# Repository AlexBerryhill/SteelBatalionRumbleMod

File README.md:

# SteelBatalionRumbleMod
 A KiCad8 pcb for the steel batalion rumble controller mod for the X-Box
 
Based off of the protoboard built in https://web.archive.org/web/20160402001949/http://www.bigmech.com/sb/sb_controller_mod/disclaimer.html

production folder in RumbleMod Folder holds everything needed to print in JLCPCB.

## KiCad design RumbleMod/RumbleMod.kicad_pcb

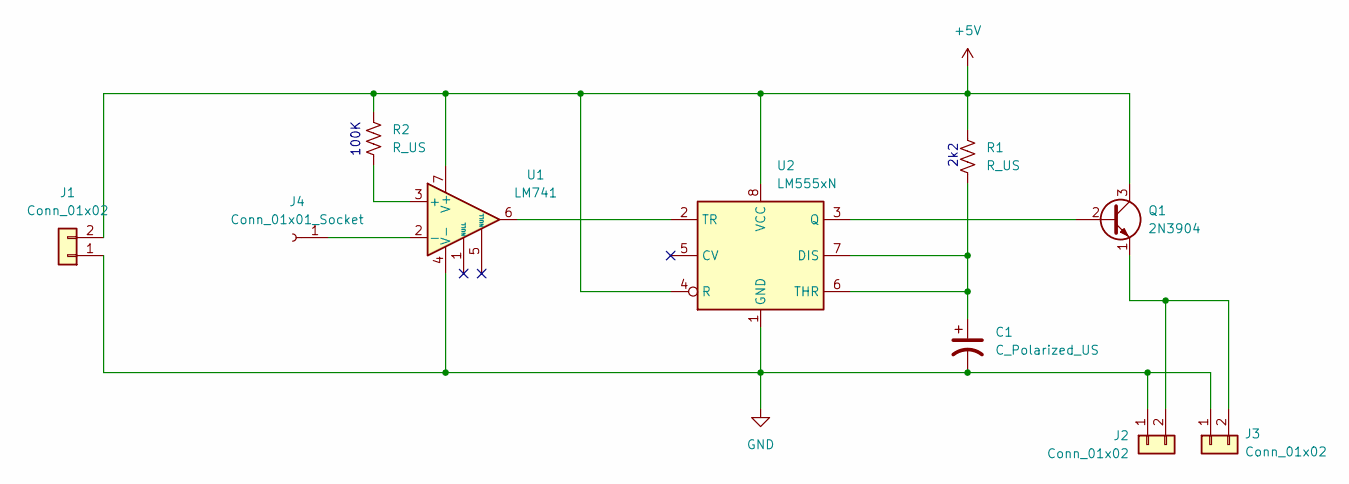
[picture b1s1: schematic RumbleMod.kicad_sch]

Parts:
C1: C_Polarized_US
J1, J2, J3: Conn_01x02; Molex_KK-254_AE-6410-02A_1x02_P2.54mm_Vertical
J4: Conn_01x01_Socket; JST_XH_B1B-XH-AM_1x01_P2.50mm_Vertical
Q1: 2N3904; TO-92_Inline
R1, R2: R_US; R_Axial_DIN0207_L6.3mm_D2.5mm_P10.16mm_Horizontal
U1: LM741; DIP-8_W7.62mm
U2: LM555xN; DIP-8_W7.62mm

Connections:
+5V: J1.2, Q1.3 (C), R1.1, R2.1, U1.7 (V+), U2.4 (R), U2.8 (VCC)
GND: C1.2, J1.1, J2.1, J3.1, U1.4 (V-), U2.1 (GND)
unnamed: J2.2, J3.2, Q1.1 (E)
unnamed: J4.1, U1.2 (-)
unnamed: Q1.2 (B), U2.3 (Q)
unnamed: R2.2, U1.3 (+)
unnamed: C1.1, R1.2, U2.6 (THR), U2.7 (DIS)
unnamed: U1.6, U2.2 (TR)

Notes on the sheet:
2k2
100K

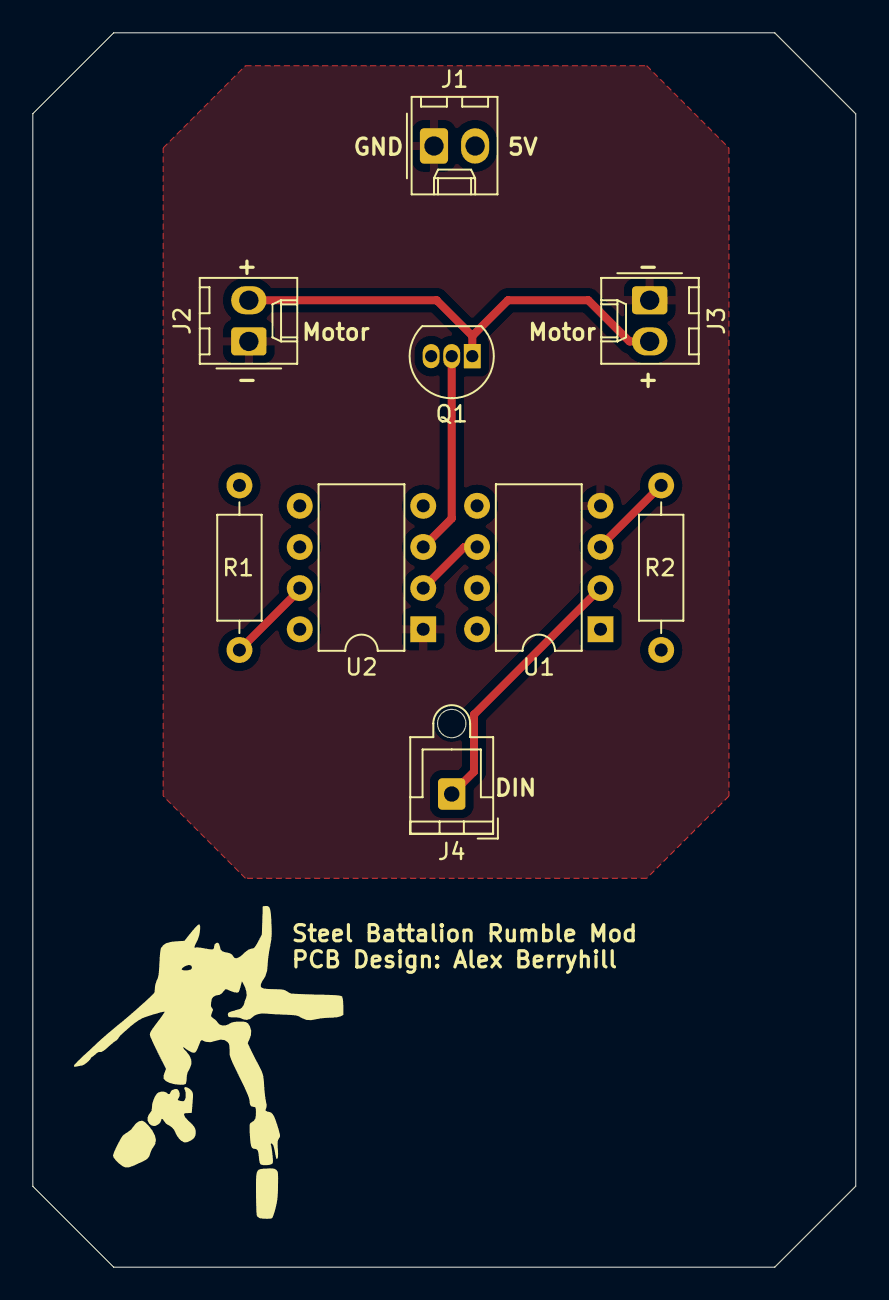
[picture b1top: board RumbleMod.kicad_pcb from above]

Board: 2 copper layers, 50.8 x 76.2 mm, 9 parts (0 on the bottom side), 8 nets.

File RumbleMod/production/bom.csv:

Designator,Footprint,Quantity,Value,LCSC Part #
"J1, J2, J3",Molex_KK-254_AE-6410-02A_1x02_P2.54mm_Vertical,3,Conn_01x02,
J4,JST_XH_B1B-XH-AM_1x01_P2.50mm_Vertical,1,Conn_01x01_Socket,
Q1,TO-92_Inline,1,2N3904,
"R1, R2",R_Axial_DIN0207_L6.3mm_D2.5mm_P10.16mm_Horizontal,2,R_US,
U1,DIP-8_W7.62mm,1,LM741,
U2,DIP-8_W7.62mm,1,LM555xN,

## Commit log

2025-03-08 V1 created
    not proper size
2025-03-10 Add production
2025-04-04 new production files
